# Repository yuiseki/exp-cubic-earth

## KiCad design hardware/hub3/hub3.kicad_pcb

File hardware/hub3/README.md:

# hub3

XIAO ESP32-S3 (1x7 のピンソケット 2 個に挿す)、74HC138、20 ピン 1.0mm の FFC コネクタ 3 個を載せた 36 x 36 mm の 2 層基板 (片面実装、穴なし)。ER-PCBA5981-1 を 3 枚つなぎ、`lt7680_multi` の構成 3 (`-DNUM_BOARDS=3`) と同じ配線にする (`WIRING.md`)。

- J1 (LCD0、左の辺)、J2 (LCD1、上の辺)、J3 (LCD2、右の辺): Ckmtw F-FPC1M20P-B310 下接 (LCSC C132515)。口は基板の外を向き、基板の辺にそろう。J2 は上の辺の中央、J1 と J3 は J2 の帯 (奥行き 7.6 mm) より下で、下の辺まで
- J4、J5: XIAO 用の 1x7、2.54 mm のメスのピンソケット (XFCN PM254V-11-07-H85、LCSC C2832270、高さ 8.5 mm)。USB-C を下の辺 (FFC の無い辺) に向けて挿すと、右の列 J4 が XIAO の 1〜7 番 (D0〜D6、D0 が下)、左の列 J5 が 8〜14 番 (D7〜5V、5V が下)。XIAO 本体 (回路図の U2) は基板に載らず、手で挿す
- U1: 74HC138 (SOIC-16、LCSC C2674688)。XIAO の下の、ソケットの 2 列の間に置く。A, B, C = D0, D2, D6。基板 b の LCM_SCS は Yb、LCD_CS は Y(3+b)、Y6 と Y7 は空き
- C1 100nF (74HC138 の 3.3V)、C2 10uF (XIAO の 5V ピンのそば)。どちらも XIAO の下
- 取り付け穴は無い

大きさは、コネクタとソケットで決まる。横は J1 の奥行き 7.9 mm (コートヤード)、ソケット 2 列の外形 18.9 mm、J3 の奥行き 7.9 mm と、そのすき間で 36 mm。縦は J2 の帯 7.6 mm と J1、J3 の長さ 28 mm で 36 mm。XIAO の下に部品を入れないと、縦は約 39 mm になる。

## 作り方

すべてスクリプトから作る。回路図と基板を手で直したら、次に `make.py` を流すと上書きされる。

```sh
/usr/bin/python3 make.py    # 回路図、部品を置いた基板、ライブラリ (KiCad 10 の pcbnew モジュールを使う)
/usr/bin/python3 route.py   # Freerouting で配線し、GND のベタを塗る
./check.sh                  # ERC、DRC (回路図との突き合わせ込み)、test_hub3.py。どれも 0 件で通る
/usr/bin/python3 fab.py     # JLCPCB 用: build/fab/ にガーバーとドリルの zip、BOM、部品配置 (CPL)
```

- 部品と網の表は `make.py` の先頭にあり、回路図と基板の両方がそこから作られる
- `test_hub3.py` は `make.py` とは別に、`WIRING.md` の配線表から各パッドの網を確かめる
- Freerouting は Linux 向けの実行環境同梱版 (`freerouting-2.4.1-linux-x64.zip`) を `~/.local/share/freerouting/2.4.1/` に置いて使う。jar 単体は Java 25 が要る
- 配線するときは GND のベタを外し、GND も線で引いてからベタを戻す。ベタを残したまま渡すと、Freerouting は GND を引かず、表のベタが島に分かれる
- Freerouting は、`make.py` で作るたびに違う配線を返し、ときどき島や未接続を残したり、電源の線を FFC のパッドの手前で長く細らせたりする。`route.py` は、KiCad の DRC が 0 件で、+5V と +3V3 の 0.6 mm 未満の区間が合わせて 7.5 mm (FFC コネクタ 1 個あたり約 2.5 mm) 以下になるまで、最大 8 回やり直す。Freerouting は同じ DSN なら設定や網の順を変えても同じ結果を返すが、`make.py` が作るたびに部品の内部 ID が変わって DSN も変わるので、やり直すときは `make.py` から作り直す。1 回ごとに別のプロセスで動かす (pcbnew の SWIG は、同じプロセスで基板を読み直して編集すると落ちる)
- 部品配置 (CPL) とガーバーの原点は基板の左下の角。SOIC-16 と 1x7 のピンソケットは JLCPCB の 0 度が KiCad と 90 度ずれるので、CPL で 90 度補正している (`fab.py` の `JLC_ROTATION_OFFSET`、JLCPCB の確認画面で見つけた)。BOM と CPL は LCSC の番号がある部品 (U1、C1、C2、J1〜J5)。J4、J5 は挿入部品 (THT) なので、JLCPCB の組み立てで挿入部品を受けてもらう

## 発注の前に確かめること

実物 (rev B) では、下の 1 番の向きの判断は誤りだった。両端の接点が同じ面にあるケーブルでつなぐと、コネクタの n 番は ER-PCBA5981-1 の CON1 の 21-n 番につながる。テスターで、CON1 の GND (JP1 の 1 番) と XIAO の D4 (コネクタの 19 番、LCD_SCLK) が導通した。このまま電源を入れると、5V (コネクタの 3、4 番) が CON1 の 18 番 (LCD_DIN) と 17 番に入り、ER-PCBA5981-1 には GND が届かない。3.3V の網 (JP1 の 6 番) は信号線からの漏れで約 1.6V になり、LT7680 は応答しない (STSR=0xFF)。両端の接点が反対の面にあるケーブルに替えると、3 枚とも LT7680 が応答して映った (2026-10-28、`lt7680_multi` の `NUM_BOARDS=3`、STSR=0x54)。今の基板は、このケーブルで使う。

以下は発注前に書いた判断 (誤り)。

- FFC の 1 番の向き。この基板は「コネクタの n 番 = ER-PCBA5981-1 の CON1 の n 番」としている。根拠: 今つないでいる変換基板 (FPC-20P 1.0MM) のコネクタは C132515 と同じ下接で (本人の確認、2026-10-19)、1 番も口から見て同じ側 (口を上にして左) にある (写真のシルクの 10 と 20 の位置から読んだ)。その変換基板で、同じケーブル (両端の接点が同じ面) を使って「変換基板の j 番 = CON1 の j 番」で動いている。この対応はケーブルの引き回し (曲げ、折り返し、ねじり) では変わらない。ケーブルの片端を裏返して挿すと、接点がコネクタの接点に当たらず、どこにもつながらない (`../../WIRING.md`)。n 番が 21-n 番につながるのは、両端の接点が反対の面にあるケーブルを使ったときだけ
- C132515 のフットプリントは、JLCPCB の EasyEDA にある同じ部品のフットプリント (FPC-SMD_P1.00-20P_XJ-CLS) のパッドの数値で作った。JLCPCB の部品配置の確認画面で、J1〜J3 の向きを確かめる
- 74HC138 の電源は XIAO の 3.3V、FFC の VDD は XIAO の 5V (USB からそのまま)

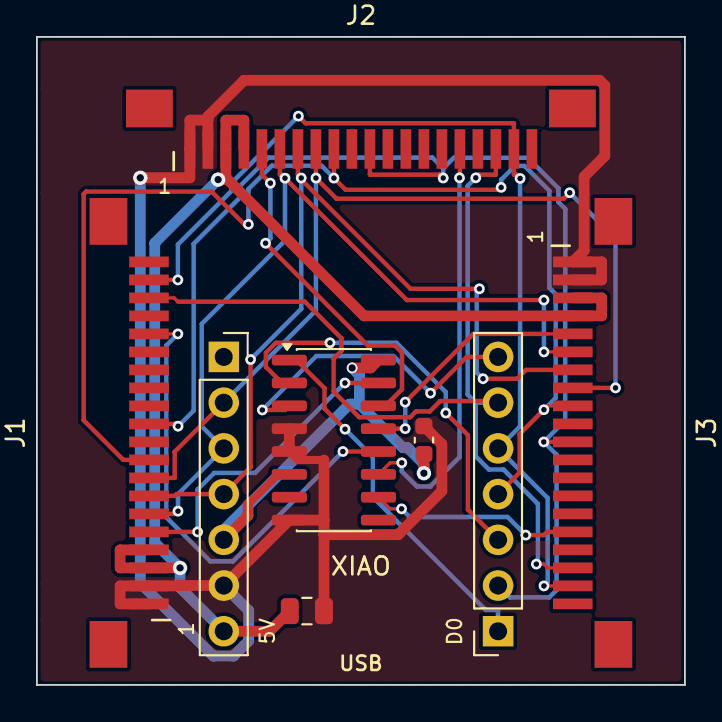
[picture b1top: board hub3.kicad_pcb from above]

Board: 2 copper layers, 36.0 x 36.0 mm, 9 parts (0 on the bottom side), 19 nets.

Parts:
C1: 100nF; C_0603_1608Metric
C2: 10uF; C_0805_2012Metric
J1: LCD0; FFC_1.0mm_20P_Bottom_C132515
J2: LCD1; FFC_1.0mm_20P_Bottom_C132515
J3: LCD2; FFC_1.0mm_20P_Bottom_C132515
J4: XIAO D0-D6; PinSocket_1x07_P2.54mm_Vertical
J5: XIAO D7-5V; PinSocket_1x07_P2.54mm_Vertical
U1: 74HC138; SOIC-16_3.9x9.9mm_P1.27mm
X1: XIAO; XIAO_ESP32S3_Outline

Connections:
+3V3: C1.1, J5.5, U1.6, U1.16
+5V: C2.1, J1.3, J1.4, J2.3, J2.4, J3.3, J3.4, J5.7
BL_CTRL: J1.9, J2.9, J3.9, J4.4
GND: C1.2, C2.2, J1.1, J1.2, J2.1, J2.2, J3.1, J3.2, J5.6, U1.4, U1.5, U1.8
LCD_CS0: J1.16, U1.12
LCD_CS1: J2.16, U1.11
LCD_CS2: J3.16, U1.10
LCD_DIN: J1.18, J2.18, J3.18, J4.6
LCD_SCLK: J1.19, J2.19, J3.19, J4.5
LCM_RESET: J1.11, J2.11, J3.11, J4.2
LCM_SCLK: J1.8, J2.8, J3.8, J5.2
LCM_SCS0: J1.5, U1.15
LCM_SCS1: J2.5, U1.14
LCM_SCS2: J3.5, U1.13
LCM_SDI: J1.7, J2.7, J3.7, J5.4
LCM_SDO: J1.6, J2.6, J3.6, J5.3
SEL_A: J4.1, U1.1
SEL_B: J4.3, U1.2
SEL_C: J4.7, U1.3

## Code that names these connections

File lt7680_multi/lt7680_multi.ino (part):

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static const int PIN_SCK    = D8;
static const int PIN_MISO   = D9;
static const int PIN_MOSI   = D10;
static const int PIN_PANEL_SCK = D4;  // CON1 19 LCD_SCLK
static const int PIN_PANEL_SDA = D5;  // CON1 18 LCD_DIN
#ifdef BOARD_SELECT_DIRECT
static const int PIN_SCS    = D0;
static const int PIN_LCD_CS = D2;
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  loadFaces();
  SPI.begin(PIN_SCK, PIN_MISO, PIN_MOSI, -1);
  setSpiDrive(SPI_DRIVE);
  digitalWrite(PIN_RESET, LOW);  // LCM_RESET は全基板で共通
  delay(LT_RESET_HOLD_MS);
  digitalWrite(PIN_RESET, HIGH);
  delay(100);
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      // 基板側のプルアップ/プルダウンの有無: 内蔵プルダウンで 1 なら外部プルアップ、内蔵プルアップで 0 なら外部プルダウン。
      // 他の 2 本は既定の待機状態 (CS High、SCLK/DIN Low) に保ったまま 1 本ずつ調べる
      const int pins[3] = {PIN_LCD_CS, PIN_PANEL_SCK, PIN_PANEL_SDA};
      const char *names[3] = {"LCD_CS", "LCD_SCLK", "LCD_DIN"};
      for (int k = 0; k < 3; k++) {
        pinMode(pins[k], INPUT_PULLDOWN);
        delay(5);
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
